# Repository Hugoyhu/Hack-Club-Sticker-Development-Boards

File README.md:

# Hack-Club-Sticker-Development-Boards
"Sticker" dev boards.
Development boards based off different chipsets, in the same shape and designs as hack club stickers.

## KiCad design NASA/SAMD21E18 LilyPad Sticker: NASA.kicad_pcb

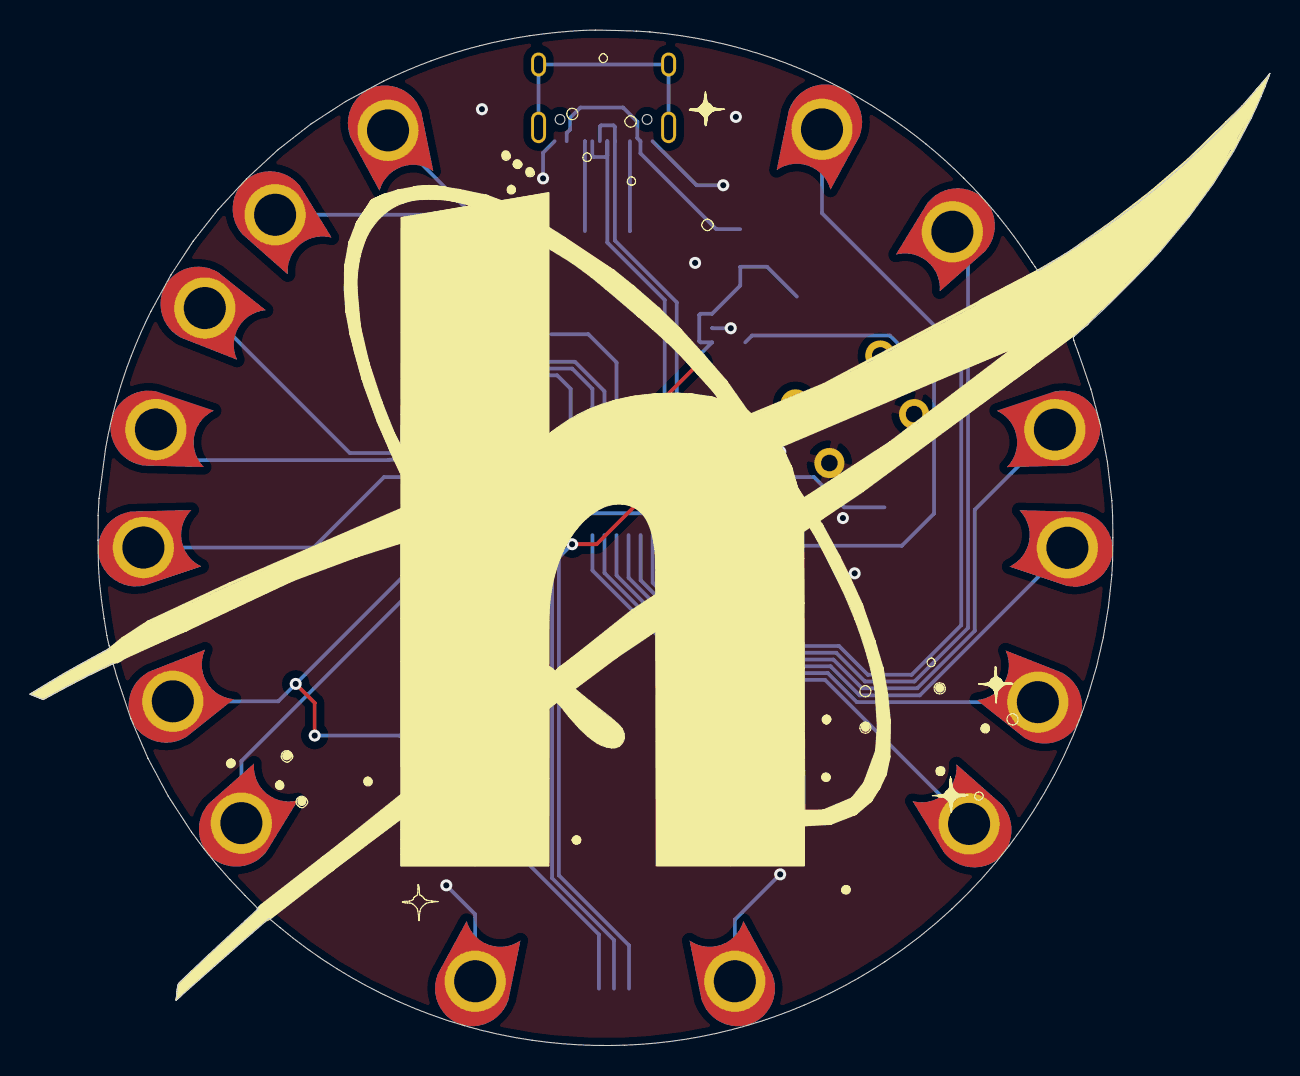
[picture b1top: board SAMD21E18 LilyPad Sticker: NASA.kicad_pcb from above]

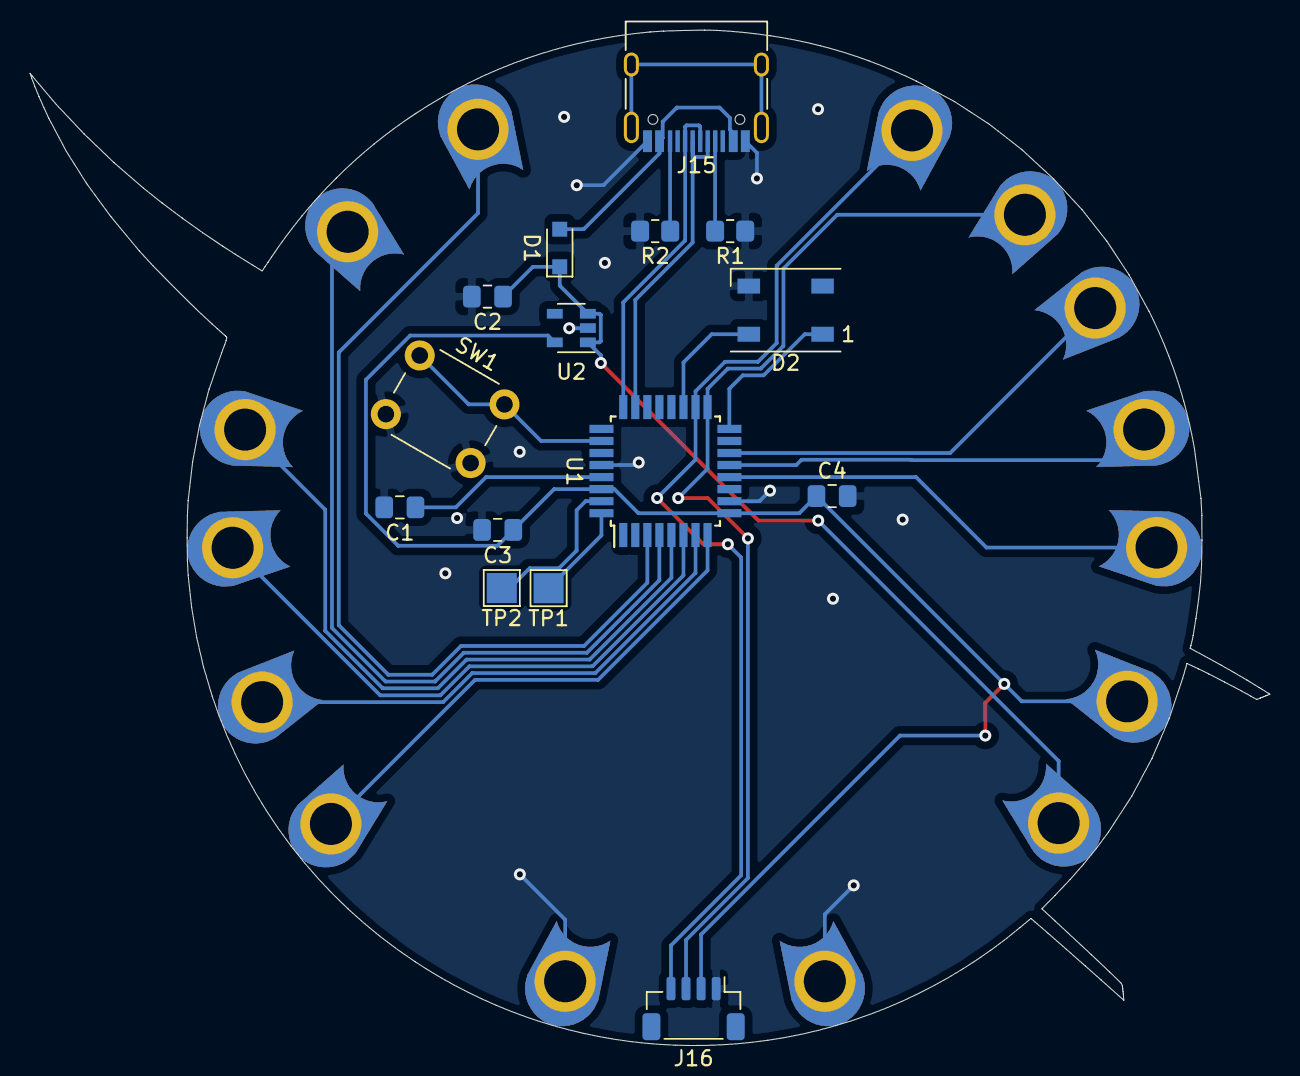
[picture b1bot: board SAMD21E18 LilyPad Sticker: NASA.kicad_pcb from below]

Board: 2 copper layers, 82.4 x 67.5 mm, 30 parts (29 on the bottom side), 25 nets.

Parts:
C1, C4: 1uF; C_0805_2012Metric_Pad1.18x1.45mm_HandSolder
C2, C3: 10uF; C_0805_2012Metric_Pad1.18x1.45mm_HandSolder
D1: NSR0320; D_SOD-323_HandSoldering
D2: WS2812B; LED_WS2812B_PLCC4_5.0x5.0mm_P3.2mm
J1, J2, J3, J4, J5, J6, J7, J8, J9, J10, J11, J12, J13, J14, J17: Conn_01x01_Female; PETAL-LONG-1-2SIDE
J15: USB_C_Receptacle_USB2.0; USB_C_Receptacle_HRO_TYPE-C-31-M-12
J16: Conn_01x04_Female; JST_SH_BM04B-SRSS-TB_1x04-1MP_P1.00mm_Vertical
R1, R2: 5.1K; R_0805_2012Metric_Pad1.20x1.40mm_HandSolder
SW1: SW_Push; SW_PUSH_6mm
TP1, TP2: TestPoint; TestPoint_Pad_2.0x2.0mm
U1: ATSAMD21E18A-A; TQFP-32_7x7mm_P0.8mm
U2: AP2112K-3.3; SOT-23-5

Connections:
+3V3: C3.1, C4.1, J3.1, J16.2, U1.9, U1.30, U2.5
+5V: C2.1, D1.1, J1.1, U2.1, U2.3
/A0: J8.1, U1.3
/A1: J9.1, U1.4
/A2: J10.1, U1.5
/A3: J11.1, U1.6
/D+: J15.A6, J15.B6, U1.24
/D-: J15.A7, J15.B7, U1.23
/MISO: J5.1, U1.12
/MOSI: J4.1, U1.13
/NEOPIX: D2.4, U1.19
/NEO_PWR: D2.1, U1.16
/RX_A7: J7.1, U1.8
/SCK: J6.1, U1.14
/SCL: J13.1, J16.4, U1.18
/SDA: J12.1, J16.3, U1.17
/SWCLK: TP2.1, U1.31
/SWDIO: TP1.1, U1.32
/TX_A6: J14.1, U1.7
GND: C1.2, C2.2, C3.2, C4.2, D2.3, J2.1, J15.A1, J15.A12, J15.B1, J15.B12, J16.1, J17.1, R1.1, R2.2, SW1.2, U1.10, U1.28, U2.2
unnamed: C1.1, U1.29
unnamed: J15.A5, R1.2
unnamed: J15.B5, R2.1
unnamed: SW1.1, U1.26
VBUS: D1.2, J15.A4, J15.A9, J15.B4, J15.B9

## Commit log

2021-03-01 Add files via upload
    Add render files
2021-03-01 [ImgBot] Optimize images
    *Total -- 256.98kb -> 144.23kb (43.88%)
    /Enjoy Hack Club/Enjoy Hack Club Sticker Design, Reverse.png -- 145.90kb -> 81.22kb (44.33%)
    /Enjoy Hack Club/Enjoy Hack Club Sticker Design, Front.png -- 111.08kb -> 63.01kb (43.28%)
2021-03-01 Add files via upload
    Add design files(kiCAD)
